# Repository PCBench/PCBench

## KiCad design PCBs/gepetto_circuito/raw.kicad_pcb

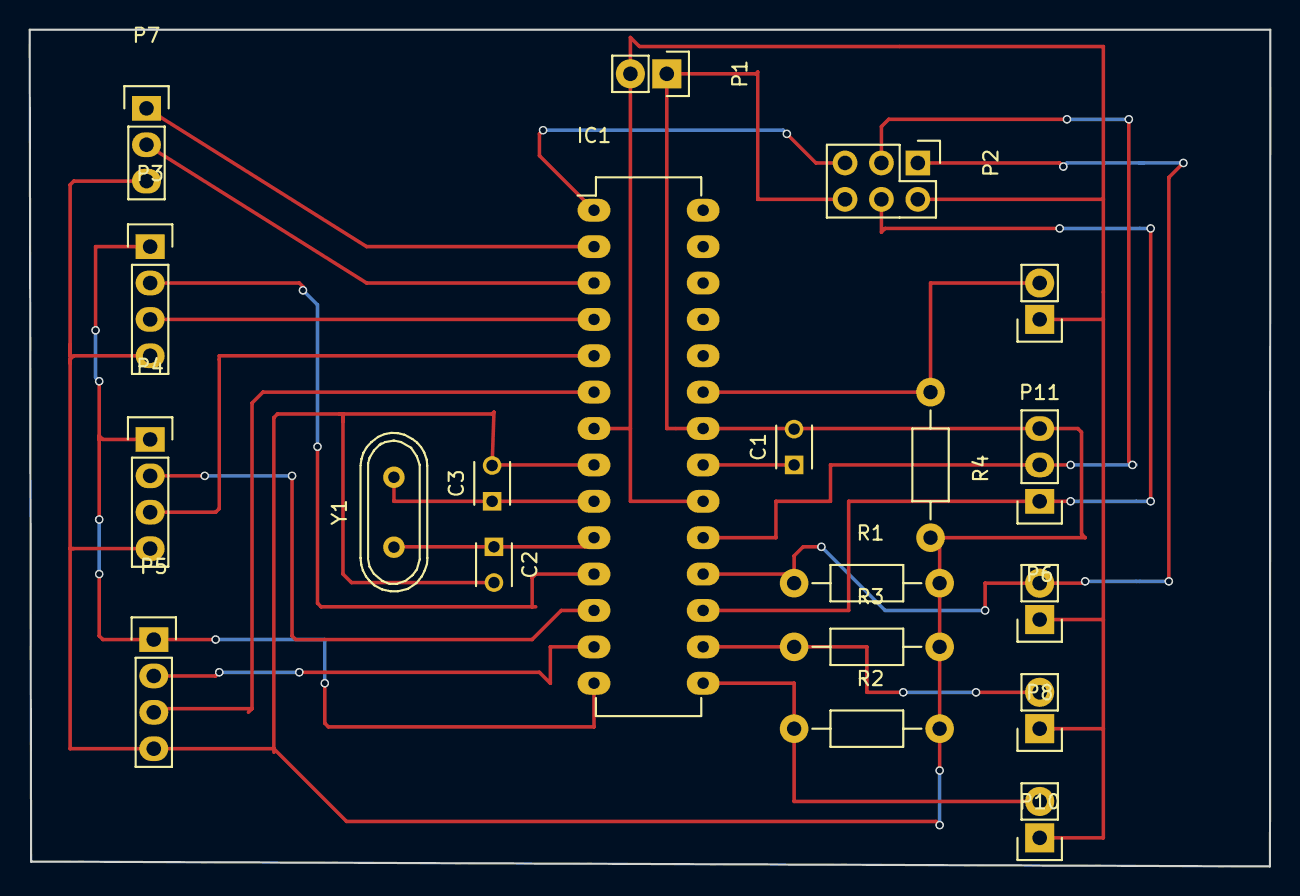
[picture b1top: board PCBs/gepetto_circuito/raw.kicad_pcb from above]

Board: 2 copper layers, 86.6 x 58.4 mm, 20 parts (0 on the bottom side), 21 nets.

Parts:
C1: 100n; C_Disc_D3_P2.5
C2, C3: 22 pF; C_Disc_D3_P2.5
IC1: ATMEGA328-P; DIP-28_W7.62mm_LongPads
P1: CONN_5V; Pin_Header_Straight_1x02
P2: CONN_02X03; Pin_Header_Straight_2x03
P3: CONN_EJE_X; Pin_Header_Straight_1x04
P4: CONN_EJE_Y; Pin_Header_Straight_1x04
P5: CONN_EJE_Z; Pin_Header_Straight_1x04
P6: CONN_HUS; Pin_Header_Straight_1x03
P7: CONN_UART; Pin_Header_Straight_1x03
P8: CONN_LIM_Z; Pin_Header_Straight_1x02
P9: CONN_LIM_X; Pin_Header_Straight_1x02
P10: CONN_LIM_Y; Pin_Header_Straight_1x02
P11: CONN_E_STOP; Pin_Header_Straight_1x02
R1, R2, R3, R4: 15 k; Resistor_Horizontal_RM10mm
Y1: 16Mhz; Crystal_HC49-U_Vertical

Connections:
/MISO: IC1.18, P2.1, P8.2, R1.1
/MOSI: IC1.17, P2.4, P6.1
/RESET: IC1.1, P2.5
/Rx_int: IC1.2, P7.1
/SCK: IC1.19, P2.3, P6.2
/Tx_int: IC1.3, P7.2
/button_stop: IC1.23, P11.2, R4.1
/dir_X: IC1.11, P3.2
/dir_Y: IC1.12, P4.2
/dir_Z: IC1.13, P5.2
/enable: IC1.14, P3.1, P4.1, P5.1
/lim_X: IC1.15, P9.2, R2.1
/lim_Y: IC1.16, P10.2, R3.1
/step_X: IC1.4, P3.3
/step_Y: IC1.5, P4.3
/step_Z: IC1.6, P5.3
GND: C1.2, C2.2, C3.2, IC1.8, IC1.22, P1.1, P2.6, P3.4, P4.4, P5.4, P6.3, P7.3, R1.2, R2.2, R3.2, R4.2
unnamed: C1.1, IC1.21
unnamed: C2.1, IC1.10, Y1.1
unnamed: C3.1, IC1.9, Y1.2
VCC: IC1.7, IC1.20, P1.2, P2.2, P8.1, P9.1, P10.1, P11.1

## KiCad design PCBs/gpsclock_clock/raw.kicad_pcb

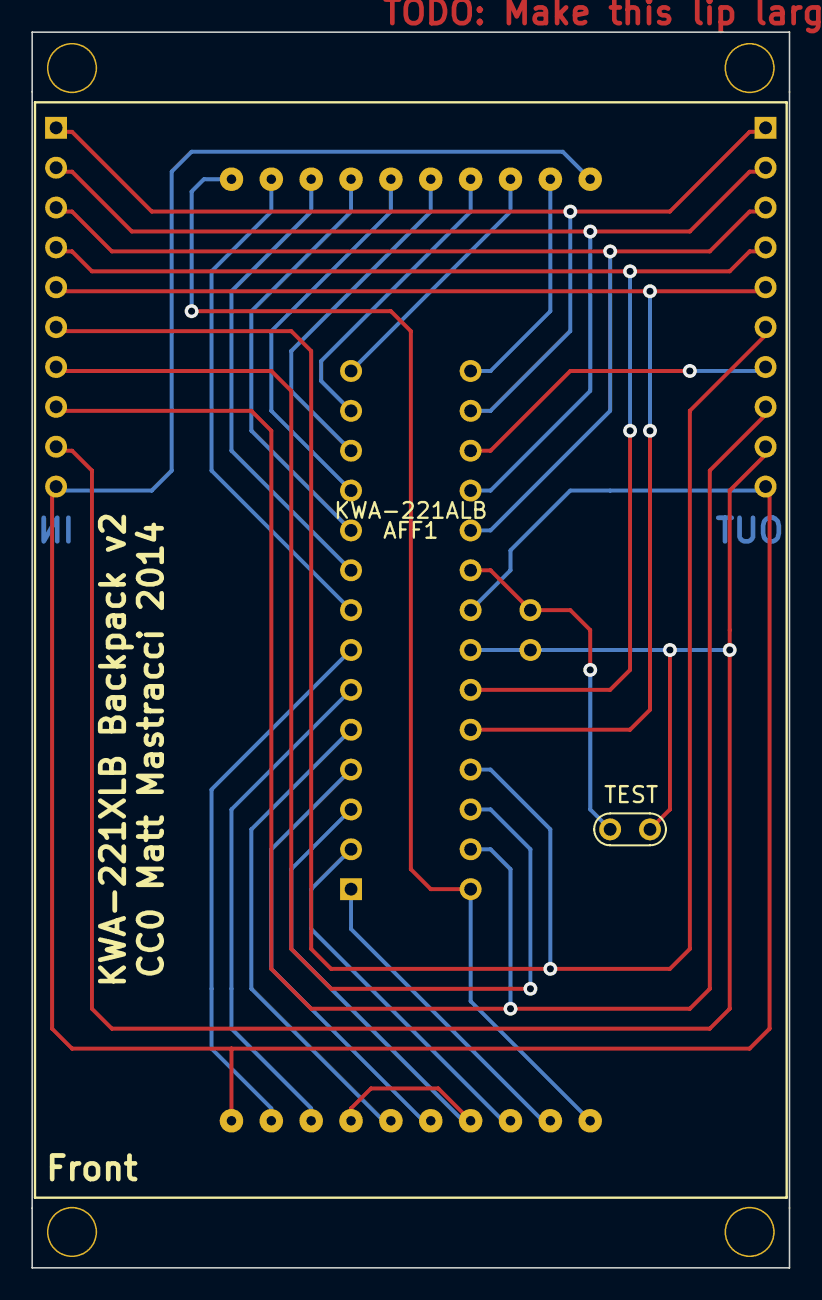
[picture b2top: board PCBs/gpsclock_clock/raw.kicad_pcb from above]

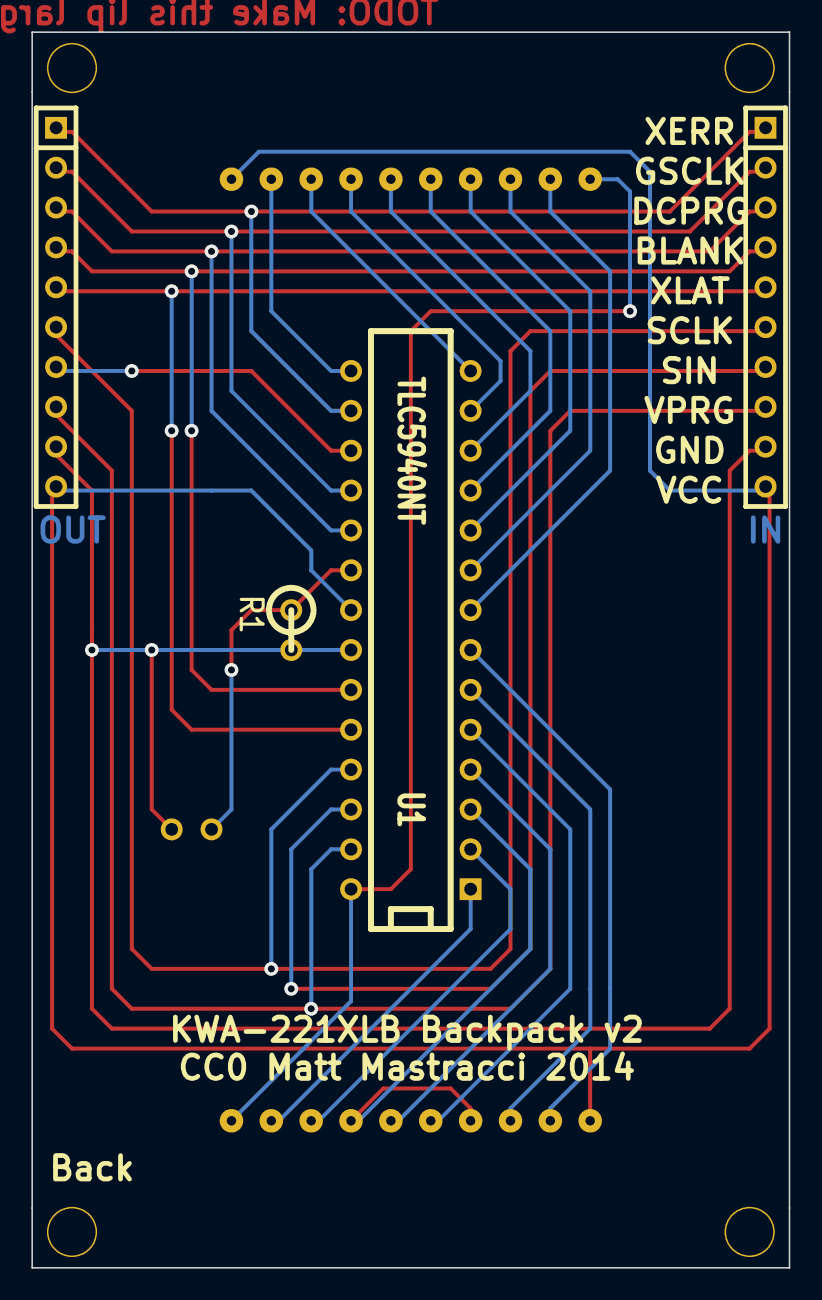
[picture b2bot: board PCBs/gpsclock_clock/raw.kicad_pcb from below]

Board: 2 copper layers, 48.3 x 78.7 mm, 10 parts (4 on the bottom side), 28 nets.

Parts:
AFF1: KWA-221ALB; KWA-221
IN1: SIL-10
MH1, MH2, MH3, MH4: MOUNTING_HOLE; 3MM_HOLE
OUT1: SIL-10
R1: R; R1
U1: TLC5940NT; DIP-28__300
W1: TEST; TEST_POINT_2PADS

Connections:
/BLANK: IN1.4, OUT1.4, U1.23
/D0: AFF1.10, AFF1.20, U1.28
/D1: AFF1.9, U1.1
/D2: AFF1.8, U1.2
/D3: AFF1.4, AFF1.7, U1.3
/D4: AFF1.6, U1.4
/D5: AFF1.5, U1.5
/D6: AFF1.3, U1.6
/D7: AFF1.2, U1.7
/D8: AFF1.19, U1.8
/D9: AFF1.18, U1.9
/D10: AFF1.17, U1.10
/D11: AFF1.16, U1.11
/D12: AFF1.15, U1.12
/D13: AFF1.14, U1.13
/D14: AFF1.13, U1.14
/D15: AFF1.12, U1.15
/DCPRG: IN1.3, OUT1.3, U1.19
/GSCLK: IN1.2, OUT1.2, U1.18
/SCLK: IN1.6, OUT1.6, U1.25
/SIN: IN1.7, U1.26
/SOUT: OUT1.7, U1.17
/VPRG: IN1.8, OUT1.8, U1.27
/XERR: IN1.1, OUT1.1, U1.16
/XLAT: IN1.5, OUT1.5, U1.24
GND: IN1.9, OUT1.9, R1.2, U1.22, W1.1
IREF: R1.1, U1.20, W1.2
VCC: AFF1.1, AFF1.11, IN1.10, OUT1.10, U1.21

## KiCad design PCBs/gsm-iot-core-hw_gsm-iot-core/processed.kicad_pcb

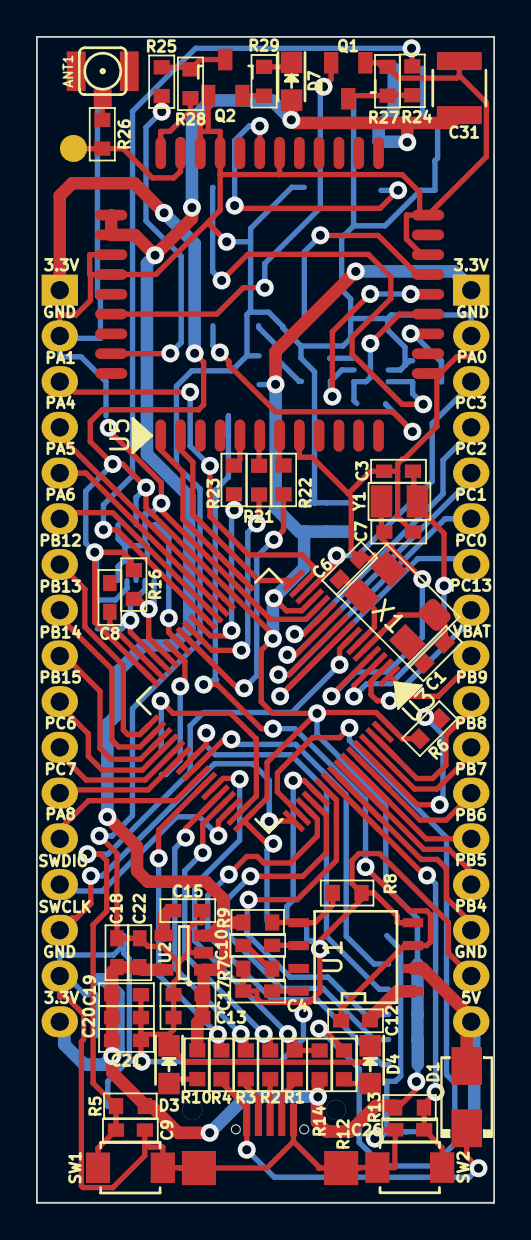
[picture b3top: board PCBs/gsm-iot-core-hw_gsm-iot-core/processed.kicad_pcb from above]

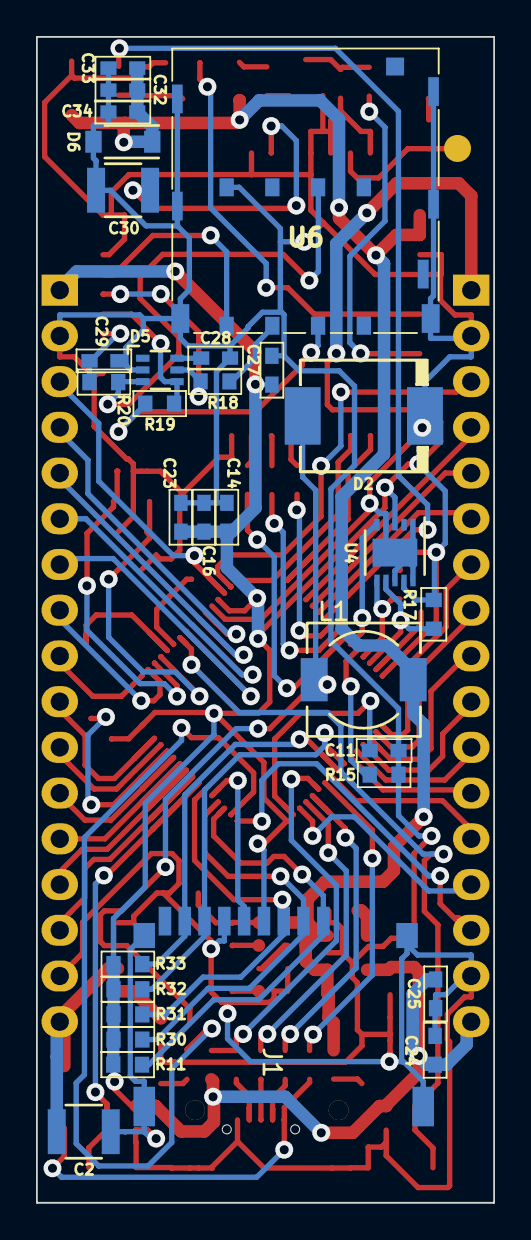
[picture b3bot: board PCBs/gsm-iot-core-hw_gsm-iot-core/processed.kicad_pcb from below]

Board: 2 copper layers, 25.4 x 64.8 mm, 92 parts (31 on the bottom side), 93 nets.

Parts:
ANT1: ANTENNA; coaxial_u.fl-r-smt-1
C1, C6, C34: 10pF; C_0603
C2: 10uF/35V; C_1210
C3, C7: 15pF; C_0603
C4: 0.1uF; C_0603
C8, C11: 2.2uF; C_0603
C9, C18, C19, C20, C21, C23, C25, C26, C27, C28: 100nF; C_0603
C10: 4.7nF; C_0603
C12, C15: 10nF; C_0603
C13: 47uF; C_0603
C14, C16, C24: 4.7uF; C_0603
C17, C22, C32: 10uF; C_0603
C29: 22pF; C_0603
C30, C31: 100uF; C_1210
C33: 33pF; C_0603
CONN1: MICRO_USB; Micro_usb_B_smd
D1: SS34; do214ac
D2: MBRS340; do214ab
D3: Led_pwr; LED_0805
D4: PA15_LED; LED_0805
D5: SMF05C; SC-70-6
D6: zener 5.1v/500mW; SOD-123
D7: Led_SIM; LED_0805
J1: MICRO_SD_HINGE - Micro SD socket Push-Push A; MicroSD_Push-Push-A
L1: 4.7uH-2.2A; Choke_SMD_6.3x6.3_H3
P1, P2: CONN_01X17; Pin_Header_Straight_1x17
P3: Chip anten; point_test
Q1, Q2: 2SC1815; SOT-23
R1: DNF-1K; R_0603
R2, R3, R18, R19, R20: 22R; R_0603
R4, R21, R22, R23: 1K; R_0603
R5, R10: 10k; R_0603
R6, R13, R15, R29: 10K; R_0603
R7: 20k; R_0603
R8: 10k-1%; R_0603
R9: 33,6k-1%; R_0603
R11, R30, R31, R32, R33: 47K; R_0603
R12: 560R; R_0603
R14: 100k; R_0603
R16, R17, R24, R27: 4.7k; R_0603
R25, R28: 4k7; R_0603
R26: 0R; R_0603
SW1, SW2: SW_PUSH; SW_SPST_B3U-1000P-B
U1: MP2365DN; SOIC-8-N
U2: LP2985-50DBVR; SOT-23-5
U3: STM32F405RGTx; TQFP-64_10x10mm_Pitch0.5mm
U4: MMA7660; DFN-10-1EP_3x3mm_Pitch0.5mm
U5: SIM800C
U6: SIM HOLD - PPSS-6P; 115I-AEAA
X1: CRYSTAL-24M; Crystal_SMD_5032_4Pads
Y1: 32.768MHz; crystal_smd_32.768_2Pin

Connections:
+3V3: C14.1, C16.1, C18.1, C19.1, C20.1, C21.1, C22.1, C23.1, C24.1, C25.1, C27.1, J1.4, P1.1, P1.17, P2.1, R5.1, R6.1, R11.2, R13.2, R14.1, R16.1, R17.1, R30.2, R31.2, R32.2, R33.2, U2.5, U3.13, U3.19, U3.32, U3.48, U3.64, U4.3, U4.9
+5V: C2.1, D1.1, P2.17, U1.2
/RST: C9.1, R5.2, SW1.2, U3.7
GND: C2.2, C3.2, C4.2, C6.2, C7.2, C9.2, C11.2, C13.2, C14.2, C15.2, C16.2, C17.2, C18.2, C19.2, C20.2, C21.2, C22.2, C23.2, C24.2, C25.2, C26.2, C27.2, C28.2, C29.2, C30.2, C31.2, C32.2, C33.2, C34.2, CONN1.5, CONN1.6, D2.2, D3.1, D4.1, D5.2, D6.2, J1.6, J1.10, J1.11, J1.12, P1.2, P1.16, P2.2, P2.16, Q1.1, Q2.1, R7.2, R8.2, R15.2, R27.1, R28.2, SW1.1, SW2.2, U1.4, U2.2, U3.12, U3.18, U4.1, U4.4, U4.8, U4.10, U4.11, U5.8, U5.13, U5.19, U5.21, U5.27, U5.30, U5.31, U5.33, U5.36, U5.37, U6.5, X1.4
GSM_ANT: P3.1, R26.1, U5.32
unnamed: ANT1.1, R26.2
unnamed: C1.2, U3.5, X1.1
unnamed: C3.1, U3.3, Y1.1
unnamed: C4.1, U1.8
unnamed: C6.1, U3.6, X1.3
unnamed: C7.1, U3.4, Y1.2
unnamed: C8.1, U3.31
unnamed: C10.1, U1.6
unnamed: C10.2, R7.1
unnamed: C11.1, U3.47
unnamed: C12.1, D2.1, L1.1, U1.3
unnamed: C12.2, U1.1
unnamed: C15.1, U2.4
unnamed: C28.1, D5.6
unnamed: C30.1, U5.28
unnamed: CONN1.1, D1.2, R4.1
unnamed: CONN1.2, R3.1
unnamed: CONN1.3, R2.1
unnamed: CONN1.4, R1.1
unnamed: D3.2, R10.1
unnamed: D4.2, R12.2
unnamed: D5.3, R20.2, U6.7
unnamed: D7.1, R29.1
unnamed: Q1.3, R24.1, R27.2
unnamed: Q2.2, R29.2
unnamed: Q2.3, R25.1, R28.1
unnamed: R6.2, U3.60
unnamed: R8.1, R9.2, U1.5
unnamed: R15.1, U3.28
unnamed: R18.1, U6.2
unnamed: R19.1, U6.3
unnamed: R21.2, U5.6
unnamed: R22.2, U5.7
unnamed: R23.2, U5.5
PA0: P2.3, U3.14
PA1: P1.3, U3.15
PA4: P1.4, U3.20
PA5: P1.5, U3.21
PA6: P1.6, U3.22
PA7_PWRKEY: R24.2, U3.23
PA8: P1.13, U3.41
PA9_VBUS: R4.2, U3.42
PA10_ID: R1.2, R14.2, U3.43
PA11_DM: R3.2, U3.44
PA12_DP: R2.2, U3.45
PA13_SWDIO: P1.14, U3.46
PA14_SWCLK: P1.15, U3.49
PA15_LED: R12.1, U3.50
PB1: U3.27, U4.5
PB3_BUTTON: C26.1, R13.1, SW2.1, U3.55
PB4: P2.15, U3.56
PB5: P2.14, U3.57
PB6: P2.13, U3.58
PB7: P2.12, U3.59
PB8: P2.11, U3.61
PB9: P2.10, U3.62
PB10_SCL: R16.2, U3.29, U4.6
PB11_SDA: R17.2, U3.30, U4.7
PB12: P1.7, U3.33
PB13: P1.8, U3.34
PB14: P1.9, U3.35
PB15: P1.10, U3.36
PC0: P2.7, U3.8
PC1: P2.6, U3.9
PC2: P2.5, U3.10
PC3: P2.4, U3.11
PC6: P1.11, U3.37
PC7: P1.12, U3.38
PC8_SDIO_D0: J1.7, R32.1, U3.39
PC9_SDIO_D1: J1.8, R33.1, U3.40
PC10_SDIO_D2: J1.1, R11.1, U3.51
PC11_SDIO_D3: J1.2, R30.1, U3.52
PC12_SDIO_CK: J1.5, U3.53
PC13: P2.8, U3.2
PD2_SDIO_CMD: J1.3, R31.1, U3.54
SIM800C_CLK: D5.4, R19.2, U5.16
SIM800C_DATA: C29.1, R20.1, U5.15
SIM800C_DCD: R23.1, U3.24
SIM800C_DTR: R21.1, U3.25
SIM800C_NETLIGHT: R25.2, U5.41
SIM800C_PWRKEY: Q1.2, U5.39
SIM800C_RI: R22.1, U3.26
SIM800C_RST: D5.5, R18.2, U5.17
SIM800C_RXD: U3.16, U5.2
SIM800C_TXD: U3.17, U5.1
SIM800C_VDD: U5.18, U6.1
VBAT: P2.9, U3.1
VDD: C13.1, C17.1, C31.1, C32.1, C33.1, C34.1, D6.1, D7.2, L1.2, R9.1, R10.2, U2.1, U2.3, U5.34, U5.35

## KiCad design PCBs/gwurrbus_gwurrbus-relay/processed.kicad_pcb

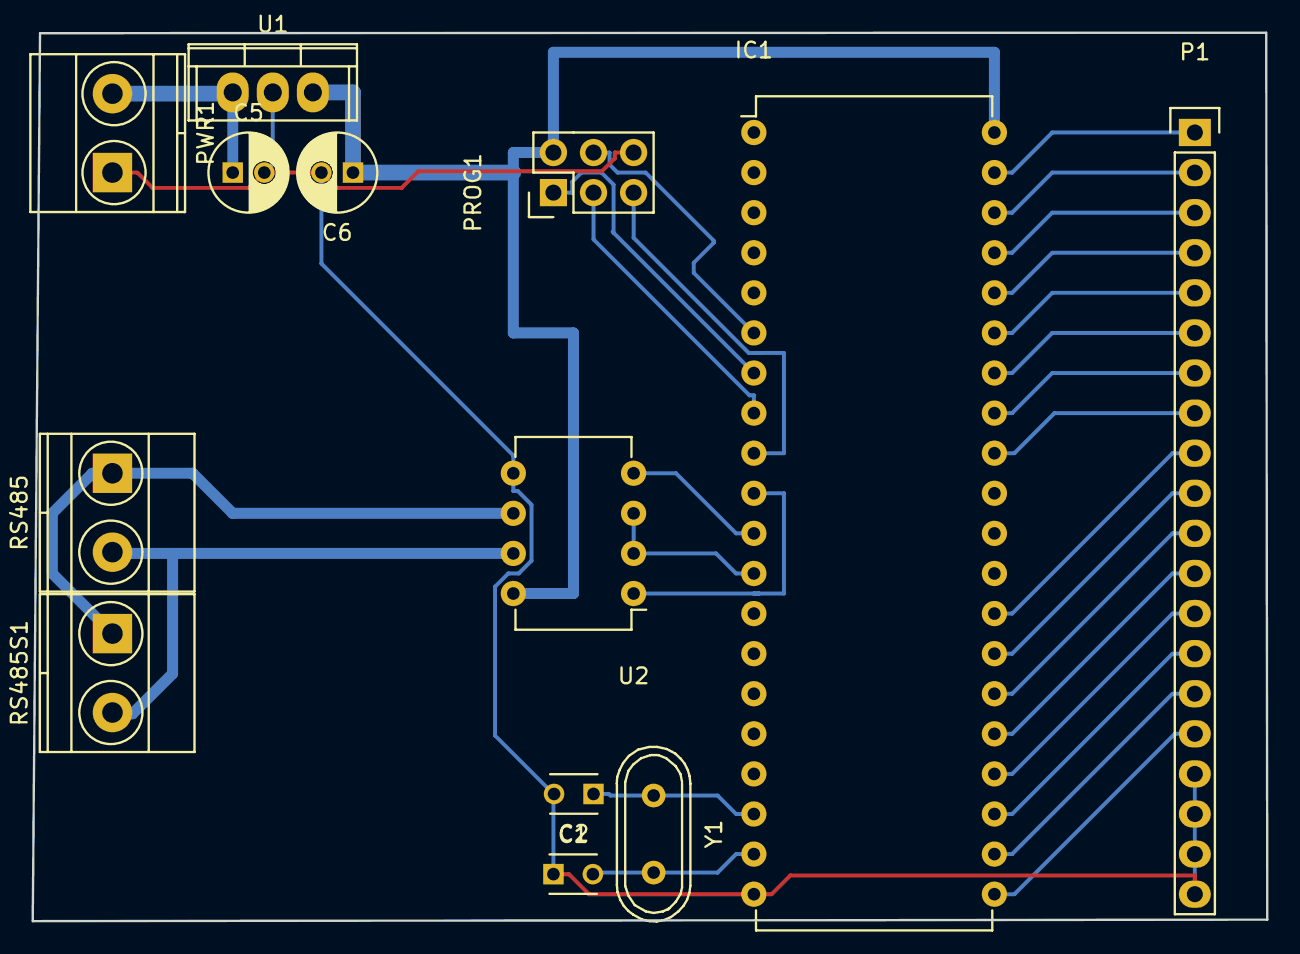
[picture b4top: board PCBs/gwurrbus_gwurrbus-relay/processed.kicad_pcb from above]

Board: 2 copper layers, 78.2 x 56.3 mm, 13 parts (0 on the bottom side), 30 nets.

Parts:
C1, C2: C_Small; C_Disc_D3_P2.5
C5, C6: 10uf; C_Radial_D5_L11_P2
IC1: AT90S8515-P; DIP-40_W15.24mm
P1: CONN_01X20; Pin_Header_Straight_1x20
PROG1: CONN_02X03; Pin_Header_Straight_2x03
PWR1: CONN_01X02; TerminalBlock_Pheonix_MKDS1.5-2pol
RS485, RS485S1: CONN_01X02; TerminalBlock_Pheonix_MKDS1.5-2pol
U1: LM7805CT; TO-220
U2: SP3485CP; DIP-8_W7.62mm
Y1: 16mhz; Crystal_HC49-U_Vertical

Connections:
+5V: C6.1, IC1.40, PROG1.2, U1.3, U2.8
+BATT: C5.1, PWR1.2, U1.1
/MISO: IC1.7, PROG1.1
/MOSI: IC1.6, PROG1.4
/O1: IC1.39, P1.1
/O2: IC1.38, P1.2
/O3: IC1.37, P1.3
/O4: IC1.36, P1.4
/O5: IC1.35, P1.5
/O6: IC1.34, P1.6
/O7: IC1.33, P1.7
/O8: IC1.32, P1.8
/O9: IC1.21, P1.16
/O10: IC1.22, P1.15
/O11: IC1.23, P1.14
/O12: IC1.24, P1.13
/O13: IC1.25, P1.12
/O14: IC1.26, P1.11
/O15: IC1.27, P1.10
/O16: IC1.28, P1.9
/RESET: IC1.9, PROG1.5
/SCK: IC1.8, PROG1.3
Earth: C1.1, C2.2, C5.2, C6.2, IC1.20, P1.17, P1.18, P1.19, P1.20, PROG1.6, PWR1.1, U1.2, U2.5
unnamed: C1.2, IC1.19, Y1.2
unnamed: C2.1, IC1.18, Y1.1
unnamed: IC1.10, U2.1
unnamed: IC1.11, U2.4
unnamed: IC1.12, U2.2, U2.3
unnamed: RS485.1, RS485S1.1, U2.6
unnamed: RS485.2, RS485S1.2, U2.7

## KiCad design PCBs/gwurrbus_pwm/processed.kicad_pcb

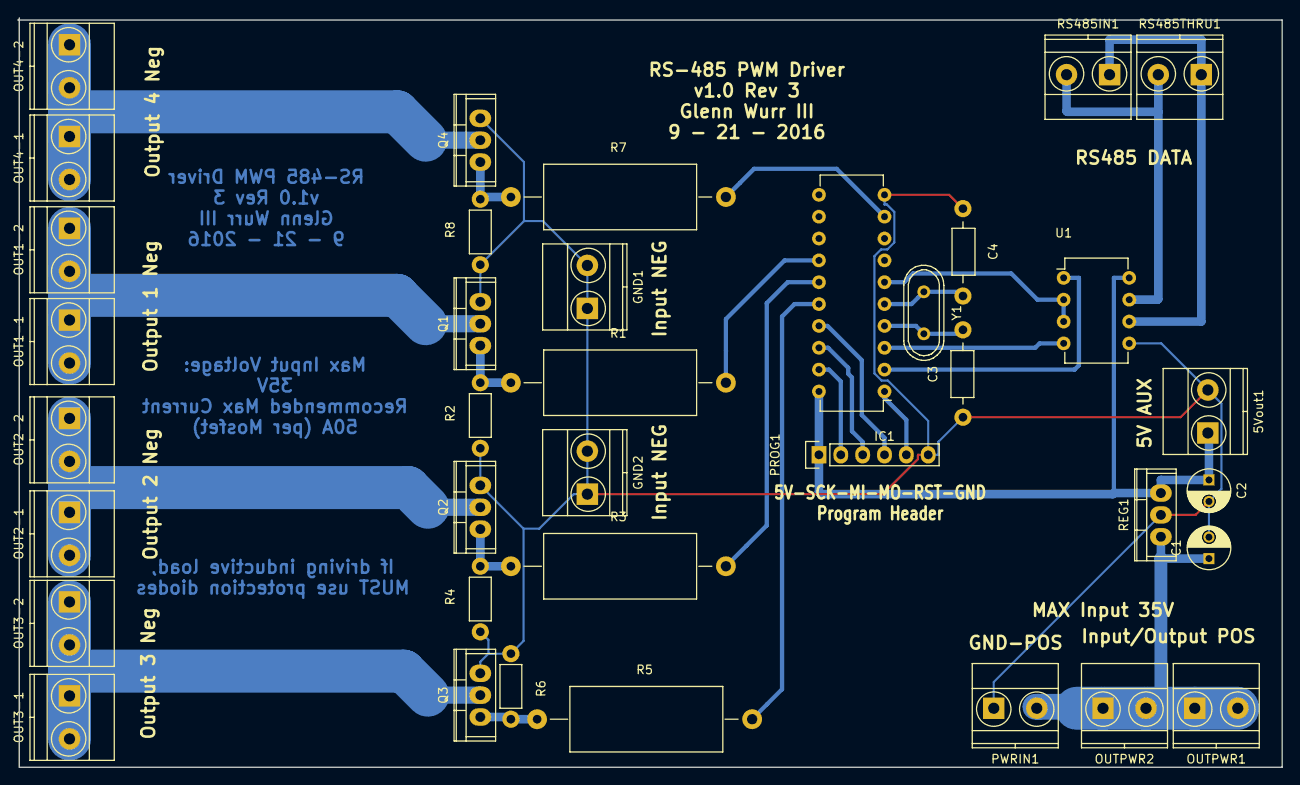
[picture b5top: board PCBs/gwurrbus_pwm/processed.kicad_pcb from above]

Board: 2 copper layers, 147.0 x 87.1 mm, 37 parts (0 on the bottom side), 26 nets.

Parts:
5Vout1: CONN_01X02; TerminalBlock_Pheonix_MKDS1.5-2pol
C1: 1uf; C_Radial_D5_L6_P2.5
C2: 10uf; C_Radial_D5_L6_P2.5
C3, C4: C_Small; Choke_Horizontal_RM10mm
GND1, GND2: CONN_01X02; TerminalBlock_Pheonix_MKDS1.5-2pol
IC1: ATTINY2313A-P; DIP-20_W7.62mm
OUT1-1, OUT1-2, OUT2-1, OUT2-2, OUT3-1, OUT3-2, OUT4-1, OUT4-2: CONN_01X02; TerminalBlock_Pheonix_MKDS1.5-2pol
OUTPWR1, OUTPWR2: CONN_01X02; TerminalBlock_Pheonix_MKDS1.5-2pol
PROG1: CONN_01X06; Pin_Header_Straight_1x06
PWRIN1: CONN_01X02; TerminalBlock_Pheonix_MKDS1.5-2pol
Q1, Q2, Q3, Q4: IRF540N; TO-220
R1, R3, R5, R7: 68R; Resistor_Horizontal_RM25mm
R2, R4, R6, R8: 2.2k; Resistor_Horizontal_RM7mm
REG1: LM7805CT; TO-220
RS485IN1, RS485THRU1: CONN_01X02; TerminalBlock_Pheonix_MKDS1.5-2pol
U1: SP3485CP; DIP-8_W7.62mm
Y1: Crystal; Crystal_HC49-U_Vertical

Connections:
+5V: 5Vout1.1, C2.1, IC1.20, PROG1.1, REG1.3, U1.8
/MISO: IC1.18, PROG1.3
/MOSI: IC1.17, PROG1.4
/OUT1: OUT1-1.1, OUT1-1.2, OUT1-2.1, OUT1-2.2, Q1.2
/OUT2: OUT2-1.1, OUT2-1.2, OUT2-2.1, OUT2-2.2, Q2.2
/OUT3: OUT3-1.1, OUT3-1.2, OUT3-2.1, OUT3-2.2, Q3.2
/OUT4: OUT4-1.1, OUT4-1.2, OUT4-2.1, OUT4-2.2, Q4.2
/PWM1: IC1.14, R1.2
/PWM2: IC1.15, R3.2
/PWM3: IC1.16, R5.2
/PWM4: IC1.9, R7.2
/RESET: IC1.1, PROG1.5
/RS485A: RS485IN1.1, RS485THRU1.1, U1.6
/RS485B: RS485IN1.2, RS485THRU1.2, U1.7
/SCK: IC1.19, PROG1.2
Earth: 5Vout1.2, C1.2, C2.2, C3.1, C4.1, GND1.1, GND1.2, GND2.1, GND2.2, IC1.10, PROG1.6, PWRIN1.1, Q1.3, Q2.3, Q3.3, Q4.3, R2.1, R4.1, R6.1, R8.1, REG1.2, U1.5
unnamed: C3.2, IC1.4, Y1.2
unnamed: C4.2, IC1.5, Y1.1
unnamed: IC1.2, U1.1
unnamed: IC1.3, U1.4
unnamed: IC1.6, U1.2, U1.3
unnamed: Q1.1, R1.1, R2.2
unnamed: Q2.1, R3.1, R4.2
unnamed: Q3.1, R5.1, R6.2
unnamed: Q4.1, R7.1, R8.2
VCC: C1.1, OUTPWR1.1, OUTPWR1.2, OUTPWR2.1, OUTPWR2.2, PWRIN1.2, REG1.1

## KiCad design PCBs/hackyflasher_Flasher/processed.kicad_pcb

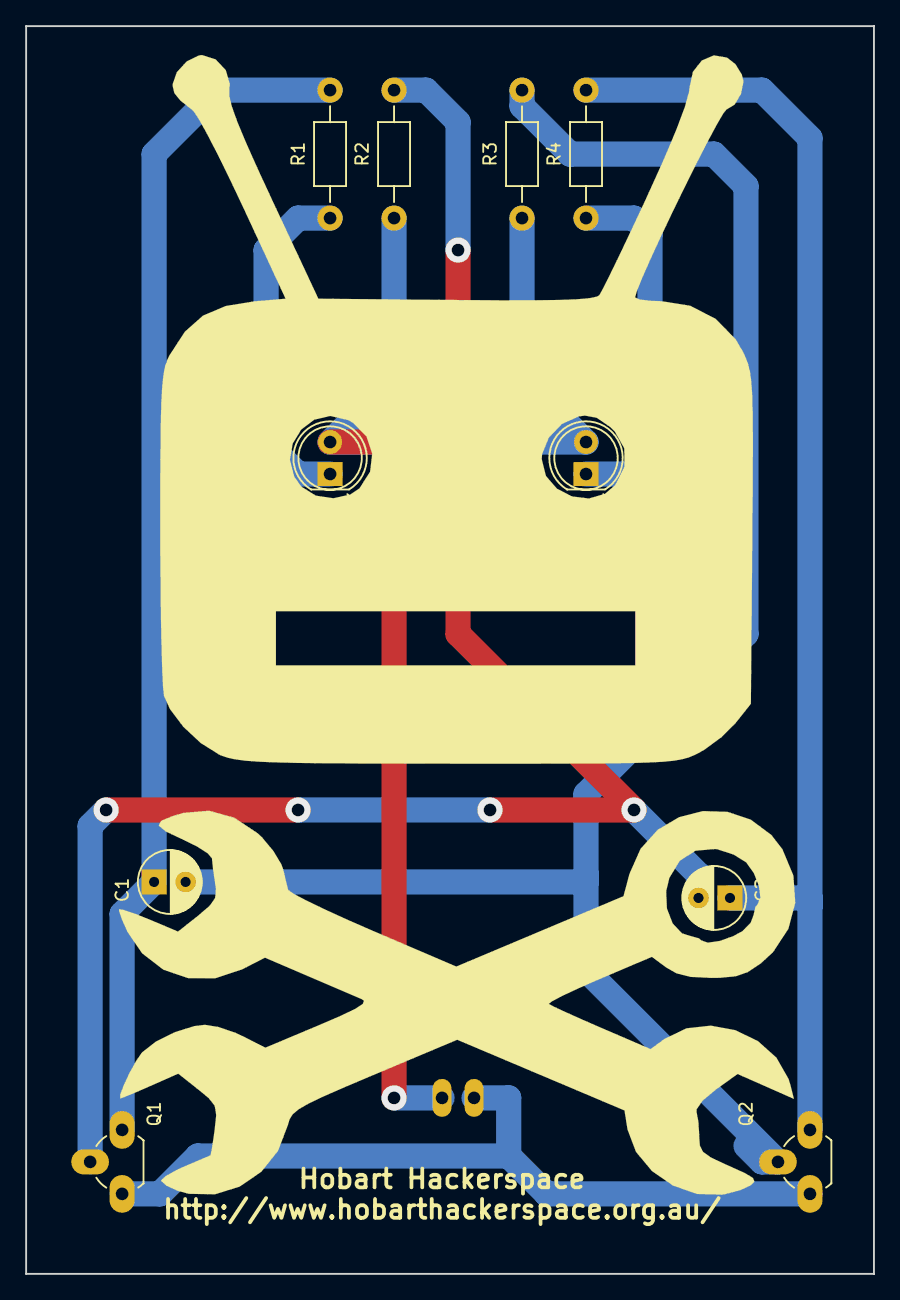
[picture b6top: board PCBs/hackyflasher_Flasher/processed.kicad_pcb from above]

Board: 2 copper layers, 67.3 x 99.1 mm, 11 parts (1 on the bottom side), 8 nets.

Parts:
BT1: 9V Battery; PINHEAD1-2
C1, C2: 10uF; C_Radial_D5_L6_P2.5-large-pads
D1, D2: LED; LED-5MM
Q1, Q2: 2N3904; TO-92_Rugged
R1, R4: 470; Resistor_Horizontal_RM10mm
R2, R3: 100k; Resistor_Horizontal_RM10mm

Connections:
+9V: BT1.1, D1.2, D2.2, R2.1, R3.1
GND: BT1.2, Q1.1, Q2.1
unnamed: C1.1, Q1.3, R1.2
unnamed: C1.2, Q2.2, R3.2
unnamed: C2.1, Q2.3, R4.2
unnamed: C2.2, Q1.2, R2.2
unnamed: D1.1, R1.1
unnamed: D2.1, R4.1
